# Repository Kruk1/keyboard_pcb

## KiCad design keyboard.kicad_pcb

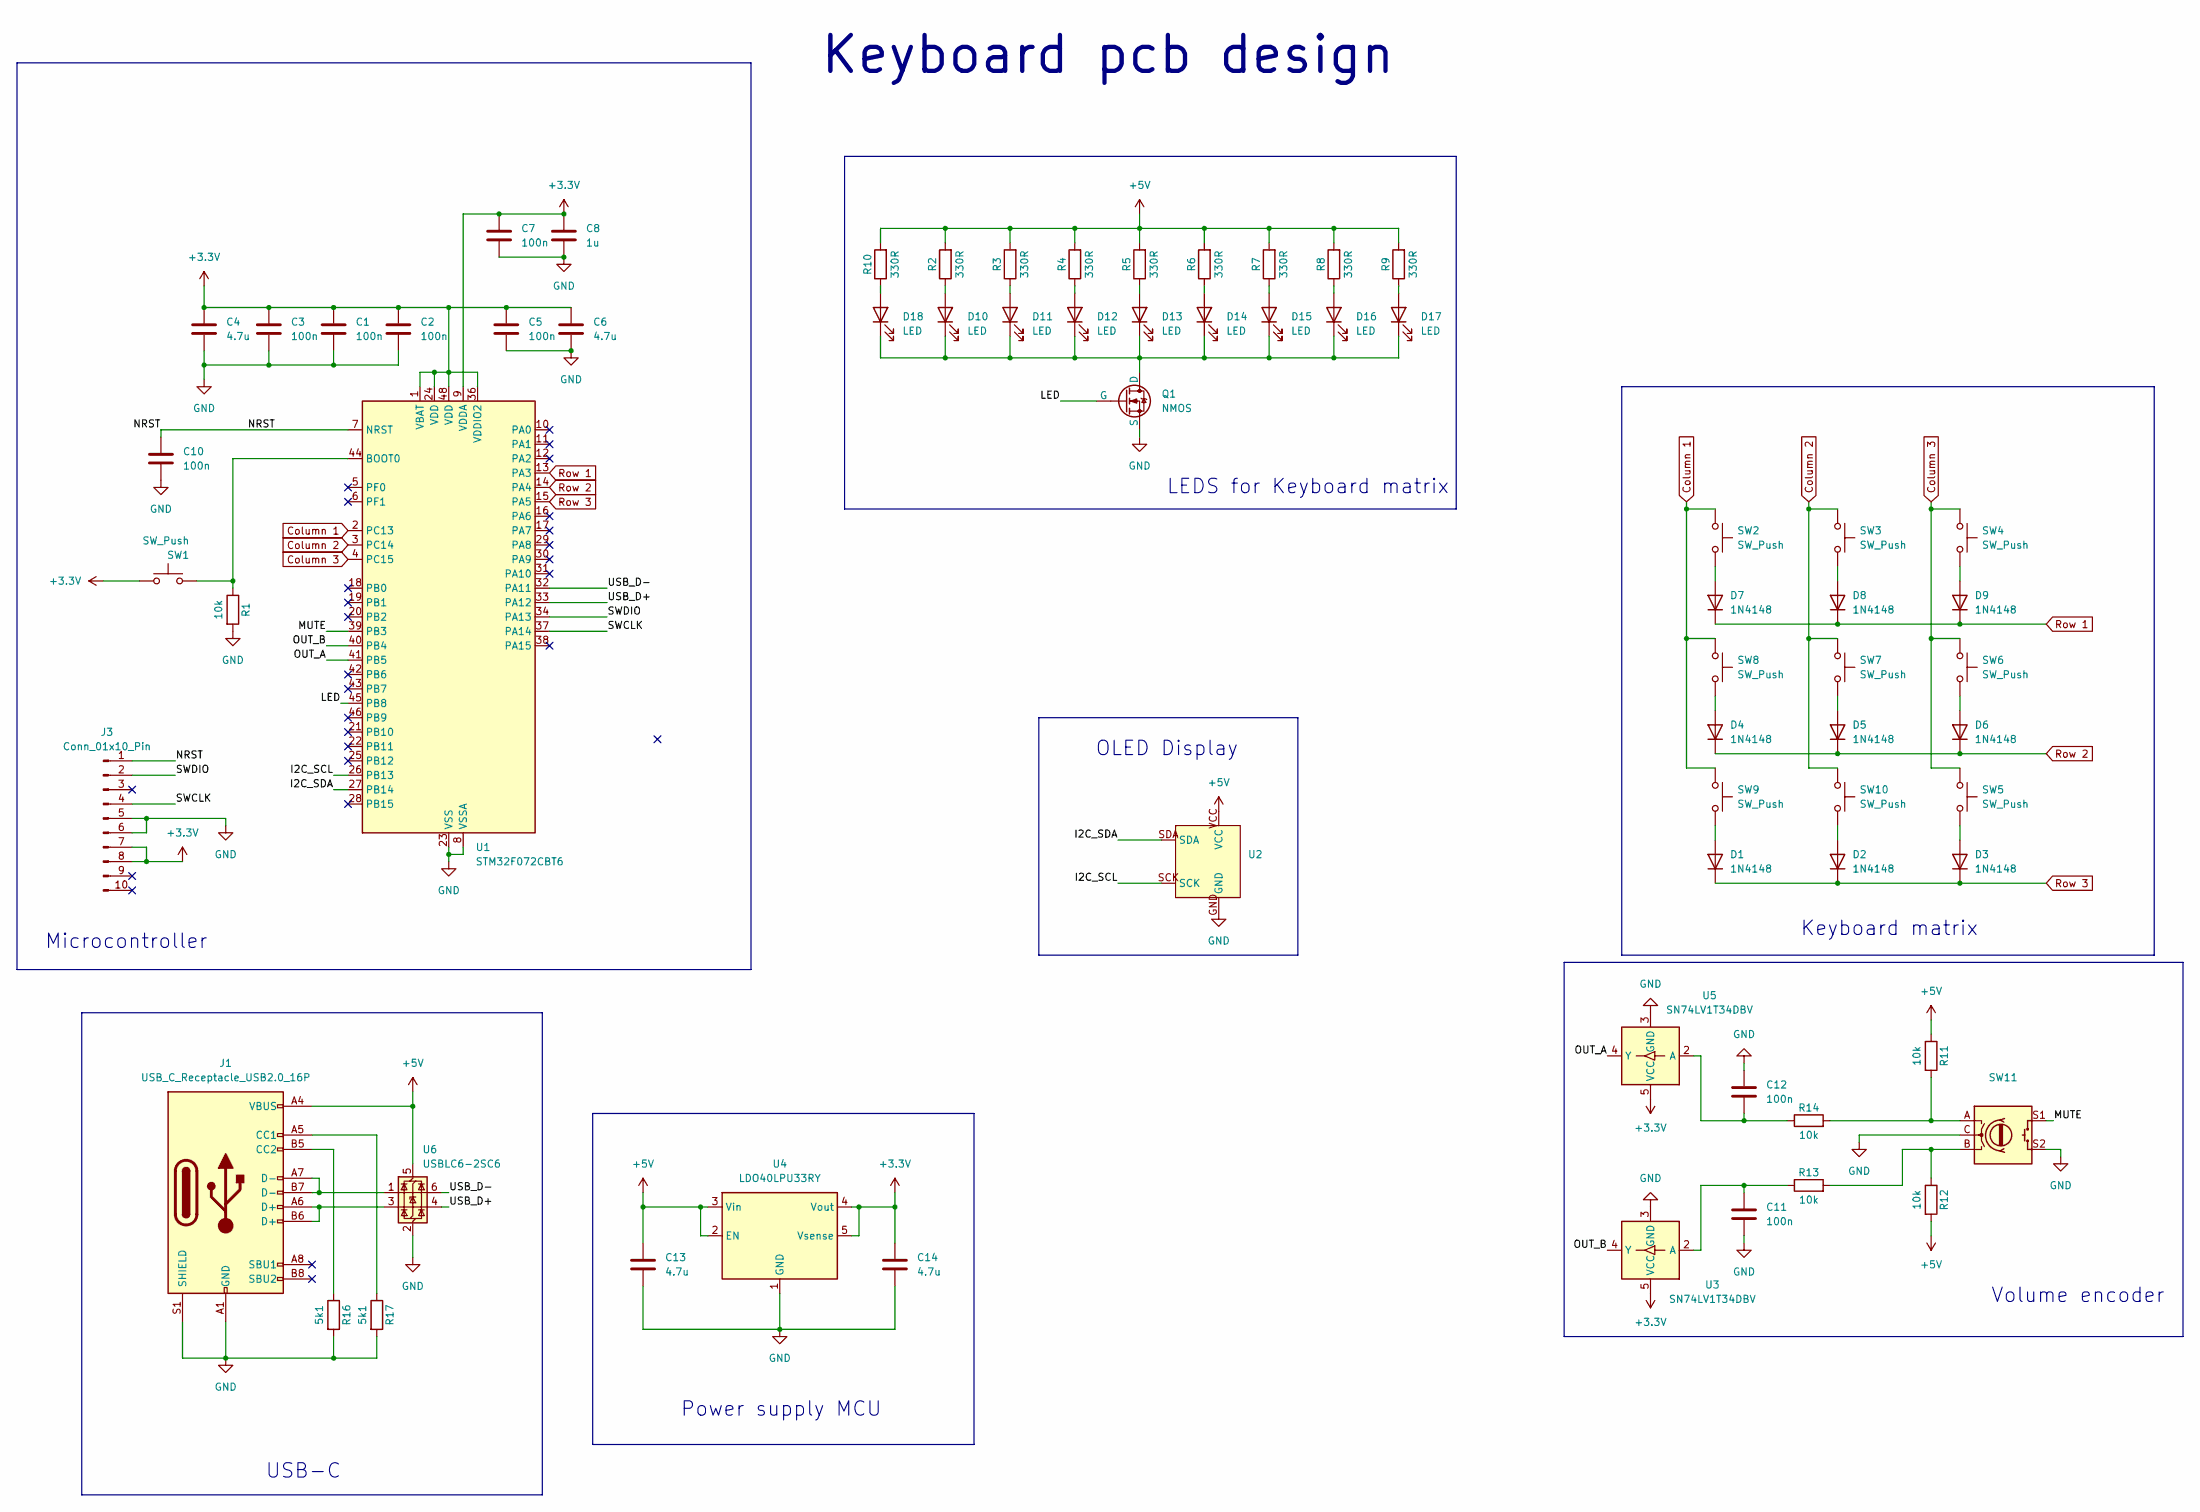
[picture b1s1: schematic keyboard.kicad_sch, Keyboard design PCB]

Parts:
C1, C2, C3, C5, C7, C10, C11, C12: 100n; C_0402_1005Metric; Mouser Part Number 81-GRM022C81A104ME5L
C4, C6, C13, C14: 4.7u; C_0805_2012Metric; Mouser Part Number 81-GRM21R61A475KE34D
C8: 1u; C_0402_1005Metric; Mouser Part Number 81-GXT155R61A105KE1D
D1, D2, D3, D4, D5, D6, D7, D8, D9: 1N4148; D_DO-35_SOD27_P7.62mm_Horizontal
D10, D11, D12, D13, D14, D15, D16, D17, D18: LED; LED_D3.0mm; Mouser Part Number 630-HLMP-Y301-F0000
J1: USB_C_Receptacle_USB2.0_16P; USB_C_Receptacle_GCT_USB4105-xx-A_16P_TopMnt_Horizontal; Mouser Part Number 640-USB4105-GF-A
J3: Conn_01x10_Pin; PinHeader_2x05_P1.00mm_Vertical; Mouser Part Number 571-17946160
Q1: NMOS; SOT95P230X110-3N; Mouser Part Number 771-NX3020NAK-QR
R1, R11, R12, R13, R14: 10k; R_0402_1005Metric; Mouser Part Number 755-ESR01MZPJ103
R2, R3, R4, R5, R6, R7, R8, R9, R10: 330R; R_0402_1005Metric; Mouser Part Number 603-RC0402JR-7D330RL
R16, R17: 5k1; R_0402_1005Metric; Mouser Part Number 71-RCC04025K10FKED
SW1: SW_Push; TS0266100BK100LCRD; Mouser Part Number 179-TS026655BK260LCR
SW2, SW3, SW4, SW5, SW6, SW7, SW8, SW9, SW10: SW_Push; SW_Cherry_MX_PCB_1.00u
SW11: RotaryEncoder_Switch; PEC12R3220FS0024; Mouser Part Number 652-PEC12R3220FS0024
U1: STM32F072CBT6; LQFP-48_7x7mm_P0.5mm
U2: Bez_nazwy
U3, U5: SN74LV1T34DBV; SOT-23-5
U4: LDO40LPU33RY; DFN-6-1EP_3x3mm_P0.95mm_EP1.7x2.6mm
U6: USBLC6-2SC6; SOT-23-6

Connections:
+3.3V: C1.1, C2.1, C3.1, C4.1, C5.1, C6.1, C7.1, C8.1, C14.1, J3.7, J3.8, SW1.1, U1.1 (VBAT), U1.9 (VDDA), U1.24 (VDD), U1.36 (VDDIO2), U1.48 (VDD), U3.5 (VCC), U4.4 (Vout), U4.5 (Vsense), U5.5 (VCC)
+5V: C13.1, J1.A4 (VBUS), J1.A9 (VBUS), J1.B4 (VBUS), J1.B9 (VBUS), R2.2, R3.2, R4.2, R5.2, R6.2, R7.2, R8.2, R9.2, R10.2, R11.1, R12.2, U2.VCC, U4.2 (EN), U4.3 (Vin), U6.5 (VBUS)
/I2C_SCL: U1.26 (PB13), U2.SCK
/I2C_SDA: U1.27 (PB14), U2.SDA
/LED: Q1.2 (G), U1.45 (PB8)
/MUTE: SW11.S1, U1.39 (PB3)
/NRST: C10.1, J3.1, U1.7 (NRST)
/OUT_A: U1.41 (PB5), U5.4 (Y)
/OUT_B: U1.40 (PB4), U3.4 (Y)
/SWCLK: J3.4, U1.37 (PA14)
/SWDIO: J3.2, U1.34 (PA13)
/USB_D+: U1.33 (PA12), U6.4 (I/O2)
/USB_D-: U1.32 (PA11), U6.6 (I/O1)
Column 1: SW2.1, SW8.1, SW9.1, U1.2 (PC13)
Column 2: SW3.1, SW7.1, SW10.1, U1.3 (PC14)
Column 3: SW4.1, SW5.1, SW6.1, U1.4 (PC15)
GND: C1.2, C2.2, C3.2, C4.2, C5.2, C6.2, C7.2, C8.2, C10.2, C11.2, C12.1, C13.2, C14.2, J1.A1 (GND), J1.A12 (GND), J1.B1 (GND), J1.B12 (GND), J1.S1 (SHIELD), J3.5, J3.6, Q1.3 (S), R1.2, R16.2, R17.2, SW11.C, SW11.S2, U1.8 (VSSA), U1.23 (VSS), U1.35 (VSS), U1.47 (VSS), U2.GND, U3.3 (GND), U4.1 (GND), U4.7 (GND), U5.3 (GND), U6.2 (GND)
unnamed: D1.2 (A), SW9.2
unnamed: D2.2 (A), SW10.2
unnamed: D3.2 (A), SW5.2
unnamed: D4.2 (A), SW8.2
unnamed: D5.2 (A), SW7.2
unnamed: D6.2 (A), SW6.2
unnamed: D7.2 (A), SW2.2
unnamed: D8.2 (A), SW3.2
unnamed: D9.2 (A), SW4.2
unnamed: D10.2 (A), R2.1
unnamed: D10.1 (K), D11.1 (K), D12.1 (K), D13.1 (K), D14.1 (K), D15.1 (K), D16.1 (K), D17.1 (K), D18.1 (K), Q1.1 (D)
unnamed: D11.2 (A), R3.1
unnamed: D12.2 (A), R4.1
unnamed: D13.2 (A), R5.1
unnamed: D14.2 (A), R6.1
unnamed: D15.2 (A), R7.1
unnamed: D16.2 (A), R8.1
unnamed: D17.2 (A), R9.1
unnamed: D18.2 (A), R10.1
unnamed: J1.A5 (CC1), R17.1
unnamed: J1.B5 (CC2), R16.1
unnamed: J1.A6 (D+), J1.B6 (D+), U6.3 (I/O2)
unnamed: J1.A7 (D-), J1.B7 (D-), U6.1 (I/O1)
unnamed: R11.2, R14.2, SW11.A
unnamed: R12.1, R13.2, SW11.B
unnamed: R1.1, SW1.2, U1.44 (BOOT0)
unnamed: C11.1, R13.1, U3.2 (A)
unnamed: C12.2, R14.1, U5.2 (A)
Row 1: D7.1 (K), D8.1 (K), D9.1 (K), U1.13 (PA3)
Row 2: D4.1 (K), D5.1 (K), D6.1 (K), U1.14 (PA4)
Row 3: D1.1 (K), D2.1 (K), D3.1 (K), U1.15 (PA5)

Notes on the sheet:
Microcontroller
USB-C
Keyboard pcb design
Keyboard matrix
Power supply MCU
OLED Display
Volume encoder
LEDS for Keyboard matrix

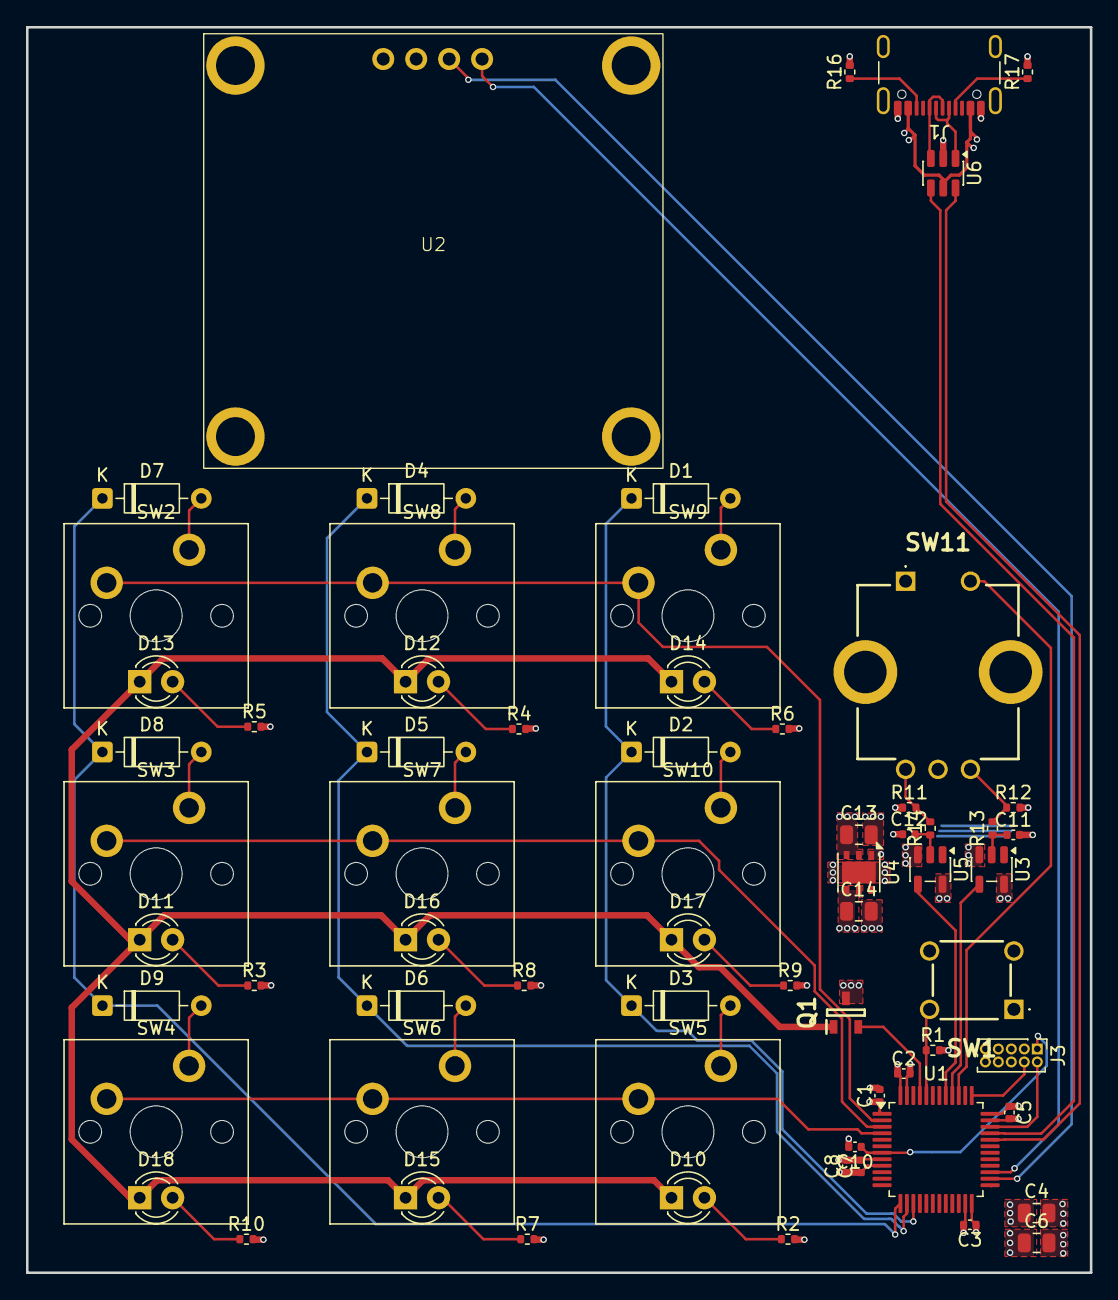
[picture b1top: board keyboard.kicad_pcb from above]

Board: 4 copper layers, 82.0 x 96.0 mm, 67 parts (0 on the bottom side), 48 nets.

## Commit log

2026-05-08 Added stm32
2026-05-09 Added keyboard matrix and leds
2026-05-09 Added rotary encoder
2026-05-09 Fix key leds
2026-05-09 Added usb-c power supply
2026-05-10 Added LDO regulator
2026-05-10 Update BOOT0 pin
2026-05-12 Added lcd display
2026-05-12 Added key switches footprints
2026-05-14 Added footprints and placement
2026-05-16 Added pcb routing
2026-05-20 Added 3D models
2026-06-01 Added oled footprint
